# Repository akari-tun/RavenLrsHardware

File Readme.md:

# Raven LRS - Hardware

Aqui podrás encontrar tanto Rx, Tx, como otro tipo de hardware compatible con RavenLRS.

## Primeros pasos en RavenLRS
Lo primero que bereras e tener es tanto un Tx como un Rx, ya sea generico o los diferentes tipos que podras encontrar en este repositorio.

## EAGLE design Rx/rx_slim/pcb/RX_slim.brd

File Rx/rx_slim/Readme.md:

# Rx Slim Rev1 (No Tested)

Este receptor es el mas pequeño que he creado hasta la fecha, siendo asi perfecto para drones de carreras tipo autobus y alas.
Esta version no cuenta con oled, por lo que no podremos visualizar los datos como en los receptores genericos de RavenLRS. <br />
**Este hardware todavía no ha sido probado**

## Listado de componentes
Ya que este proyecto es realizado en mis tiempos libre y no recivo remuneracion economica por ello, los enlaces de aliexpress llevan un enlace de afiliado, donde me dan una pequeña comision de los productos que se compren atrasves de ellos, porfavor usalos para que este proyecto siga adelante
 ### --- 433Mhz ---
 [Sx1278](https://github.com/user/repo/blob/branch/other_file.md): Emisor Lora 433Mhz con ufl incorporado. <br />
 [Esp32](https://github.com/user/repo/blob/branch/other_file.md): Procesador Esp32 con adaptador usb. (Sin oled) <br />
 [PinHead](https://github.com/user/repo/blob/branch/other_file.md): Pines para unir la pcb con el procesador. <br />
 [Condensador 1](https://github.com/user/repo/blob/branch/other_file.md): Condensadores 10uf. <br />
 [Condensador 2](https://github.com/user/repo/blob/branch/other_file.md): Condensadores 47uf. <br />
 [AMS1117](https://github.com/user/repo/blob/branch/other_file.md): Regulador 3v3. <br />
 **Tabien tendras que comprar las pcb.**

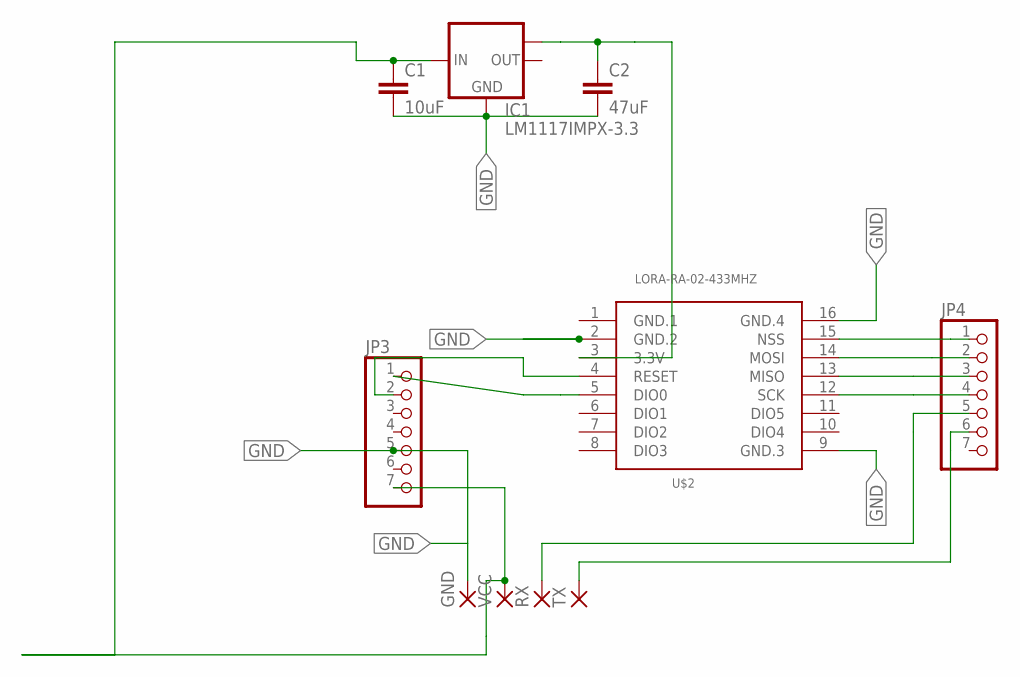
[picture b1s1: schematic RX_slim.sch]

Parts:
C1: 10uF; 0805
C2: 47uF; 0805
GND: SMD2; SMD1,27-2,54
IC1: LM1117IMPX-3.3; SOT223
JP3, JP4: PINHD-1X7; 1X07
RX: SMD2; SMD1,27-2,54
TX: SMD2; SMD1,27-2,54
U$2: LORA-RA-02-433MHZ; LORA-RA2-SMD
VCC: SMD2; SMD1,27-2,54

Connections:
GND: C1.2, C2.2, GND.1, IC1.1 (GND), JP3.5, U$2.2 (GND.2), U$2.9 (GND.3), U$2.16 (GND.4)
GND.1: U$2.1 (GND.1)
unnamed: JP3.1, U$2.5 (DIO0)
unnamed: JP4.1, U$2.15 (NSS)
unnamed: JP4.2, U$2.14 (MOSI)
unnamed: JP4.3, U$2.13 (MISO)
unnamed: JP4.4, U$2.12 (SCK)
unnamed: JP3.2, U$2.4 (RESET)
unnamed: C1.1, IC1.3 (IN), JP3.7, VCC.1
unnamed: JP4.6, TX.1
unnamed: JP4.5, RX.1
unnamed: C2.1, IC1.TAB (OUT1), U$2.3 (3.3V)

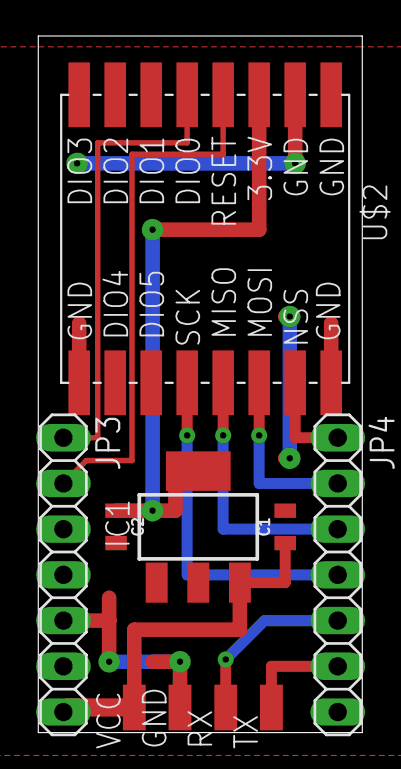
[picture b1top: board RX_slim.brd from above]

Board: 2 copper layers, 18.0 x 38.7 mm, 10 parts (0 on the bottom side), 11 nets.

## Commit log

2018-10-07 Nacimiento de rx_slim v1
    rev 1
2018-10-07 Nacimineto Rx slim

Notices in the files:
parts and their libraries:
SparkFun-Capacitors: Licensing: Creative Commons ShareAlike 4.0 International - https://creativecommons.org/licenses/by-sa/4.0
